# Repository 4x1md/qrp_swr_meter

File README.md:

# QRP SWR Meter for Yaesu FT-817ND

## Overview

This QRP SWR meter was designed for using with my Yaesu FT-817ND transceiver. Actually, it is antenna impedance meter based on Wheatstone bridge where antenna represents the unknown resistance. The bridge is built with six 2W resistors thus it can handle up to 16W of transmitting power.

This SWR-meter design has one big disadvantage: each time when SWR measurement is required, the device has to be switched from bypass to measurement mode. After antenna tuner alignment it has to be switched to bypass mode again. Real-time SWR monitoring is impossible with this type of SWR-meters. However, the Wheatstone bridge uses widely available resistors and does not require winding any coils. It makes such devices easy to build and can be considered an advantage.

## Schematic

## Reference Circuits

This project is not the first of this kind. My main source of inspiration was [Wideband SWR meter by Manfred Mornhinweg XQ6FOD](http://ludens.cl/Electron/swr/swr.html).

Other similar circuits can be found in [links section](#links) of this document and on the internet.

## Parts

In general, this circuit requires widely available easy to get parts.

The microampermeter I used for SWR indication is actually a tuning indicator from an old radio receiver. Its full deflection current is 250uA and internal resistance is about 1.2K. These values are not critical and almost any microampermeter.

Circuit alignment showed that more critical parts are diodes. The first diodes I used were BAT49 Schottky diodes. Later, due to their high capacity I had to replace them with germanium 1N60P.

## PCB Design

The PCB was designed using KiCAD software.

## Photo Gallery & Development History

### First Prototype

The first prototype was build on a random size PCB designed in KiCad Eschema. It used through hole mounted SMA female connectors.

At first, its performance was constantly starting to deteriorate at frequencies of 12-13MHz and higher. The investigation showed two main reasons:

1. I didn't clean well the PCB after soldering and the remaining flux caused current leakage at higher frequencies.
2. I used diodes with high capacity (more than 100pF).

The PCB was made at home using [toner transfer method](http://www.instructables.com/id/Cheap-and-Easy-Toner-Transfer-for-PCB-Making/).

### Second Prototype

After getting the previous prototype to work well, I decided to put the device in an enclosure box. For that matter I chose a 83x58x35mm plastic box with transparent cover which is sold cheap on AliExpress.

I had to redesign the PCB to match the inner dimensions of the box. I also decided to use right angle SMA connectors in this design. As a result I got the following prototype.

### Factory Produced PCB

Later I decided to try to order a factory produced PCB. I ordered a small quantity from ITEAD Studio. As to my taste, they did a great job.

The board fits the box perfectly.

:warning: **Important Note!**
Minimum order at the factory was 10 boards from which I need only two. As of December 1, 2016, I have 8 boards, which I can give away. If you'd like to build this SWR-meter for yourself, I can send you a board. Feel free to contact me. 

### Assembled Device

### PCB Prototypes History

All my home-made PCB prototypes in two photos.

## Links

1. [Wideband SWR meter by Manfred Mornhinweg XQ6FOD](http://ludens.cl/Electron/swr/swr.html) ([circuit 1](http://users.belgacom.net/hamradio/schemas/swrmeter.GIF))
2. [Circuit 2](https://yd1chs.files.wordpress.com/2008/12/qrp-vswr-meter-schematic.jpg)
3. [Circuit 3](http://www.radars.me.uk/Pictures/linear/Powermeter.jpg)
4. [Circuit 4](http://www.circuitdiagramworld.com/uploads/allimg/201411/135-8956_471946937.png)
5. [Measurements on Balanced Lines Using the Noise Bridge & SWR Meter by Lloyd Butler VK5BR. Amateur Radio, July 1992](http://users.tpg.com.au/users/ldbutler/MeasBalLine.htm)
6. [Low-power antenna tuner and SWR meter](http://www.tradeofic.com/Circuit/8224-LOW_POWER_ANTENNA_TUNER_AND_SWR_METER.html)
7. [Simple LED SWR bridge by John Young G0WGR](http://www.qsl.net/om3cug/swr_led/swr_meter_led_g0wqr.jpg)
8. [Измеритель КСВ by LY3BG](http://www.cqham.ru/ksw.html)
9. [КСВ-метры: теория и практика. Как сделать достоверный КСВ-метр by UT1MA](http://www.cqham.ru/ma1.phtml)
10. [Cheap and Easy Toner Transfer for PCB Making](http://www.instructables.com/id/Cheap-and-Easy-Toner-Transfer-for-PCB-Making/)
11. [Easy, Consistent & Cheap Toner Transfer Method for Single & Double Sided PCBs](http://www.instructables.com/id/Easy-Consistent-Cheap-Toner-Transfer-Method-for-Si/)

## Questions? Suggestions?
You are more than welcome to contact me with any questions, suggestions or propositions regarding this project. You can:

1. Visit [my QRZ.COM page](https://www.qrz.com/db/4X5DM)
2. Visit [my Facebook profile](https://www.facebook.com/Dima.Meln)
3. Write me an email to iosaaris =at= gmail dot com

## How to Support or Say Thanks

If you like this project, or found here some useful information and want to say thanks, or encourage me to do more, you can buy me a coffee!

You can aslo make a donation with PayPal:

---

**73 de 4X1MD ex 4X5DM**

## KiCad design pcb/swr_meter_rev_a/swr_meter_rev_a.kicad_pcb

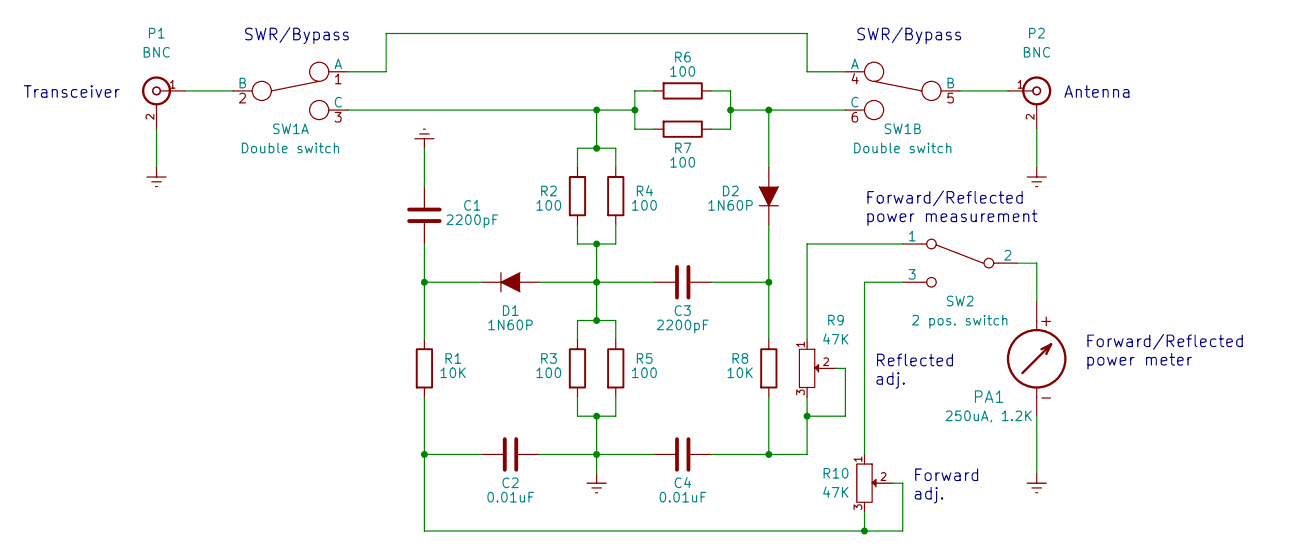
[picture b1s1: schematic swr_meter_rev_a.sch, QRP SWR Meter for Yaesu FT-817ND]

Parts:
C1: 2200pF; Capacitor_Disc_D6_P5
C2, C4: 0.01uF; Capacitor_Disc_D6_P5
C3: 2200pF; Capacitor_Disc_D6_P7.5
D1, D2: 1N60P; Diode_DO-35_SOD27_Horizontal_RM10
P1, P2: BNC; SMB_Straight
PA1: 250uA, 1.2K; Microampermeter
R1, R8: 10K; Resistor_Horizontal_RM10mm
R2, R3, R4, R5, R6, R7: 100; Resistor_Horizontal_2W
R9, R10: 47K; Potentiometer_Triwood_RM-065
SW1: Double switch; Tumbler_SW_x2
SW2: 2 pos. switch; Tumbler_SW

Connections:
GNDREF: C1.1, C2.1, C4.1, P1.2 (Ext), P2.2 (Ext), PA1.2 (-), R3.2, R5.2
unnamed: C1.2, D1.1 (K), R1.1
unnamed: C2.2, R1.2, R10.2, R10.3
unnamed: C3.1, D1.2 (A), R2.2, R3.1, R4.2, R5.1
unnamed: C3.2, D2.1 (K), R8.1
unnamed: C4.2, R8.2, R9.2, R9.3
unnamed: D2.2 (A), R6.1, R7.1, SW1.6 (C)
unnamed: P1.1 (In), SW1.2 (B)
unnamed: P2.1 (In), SW1.5 (B)
unnamed: PA1.1 (+), SW2.2
unnamed: R2.1, R4.1, R6.2, R7.2, SW1.3 (C)
unnamed: R9.1, SW2.1
unnamed: R10.1, SW2.3
unnamed: SW1.1 (A), SW1.4 (A)

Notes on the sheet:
Forward/Reflected power meter
Antenna
Transceiver
Forward/Reflected power measurement
SWR/Bypass
Forward adj.
Reflected adj.

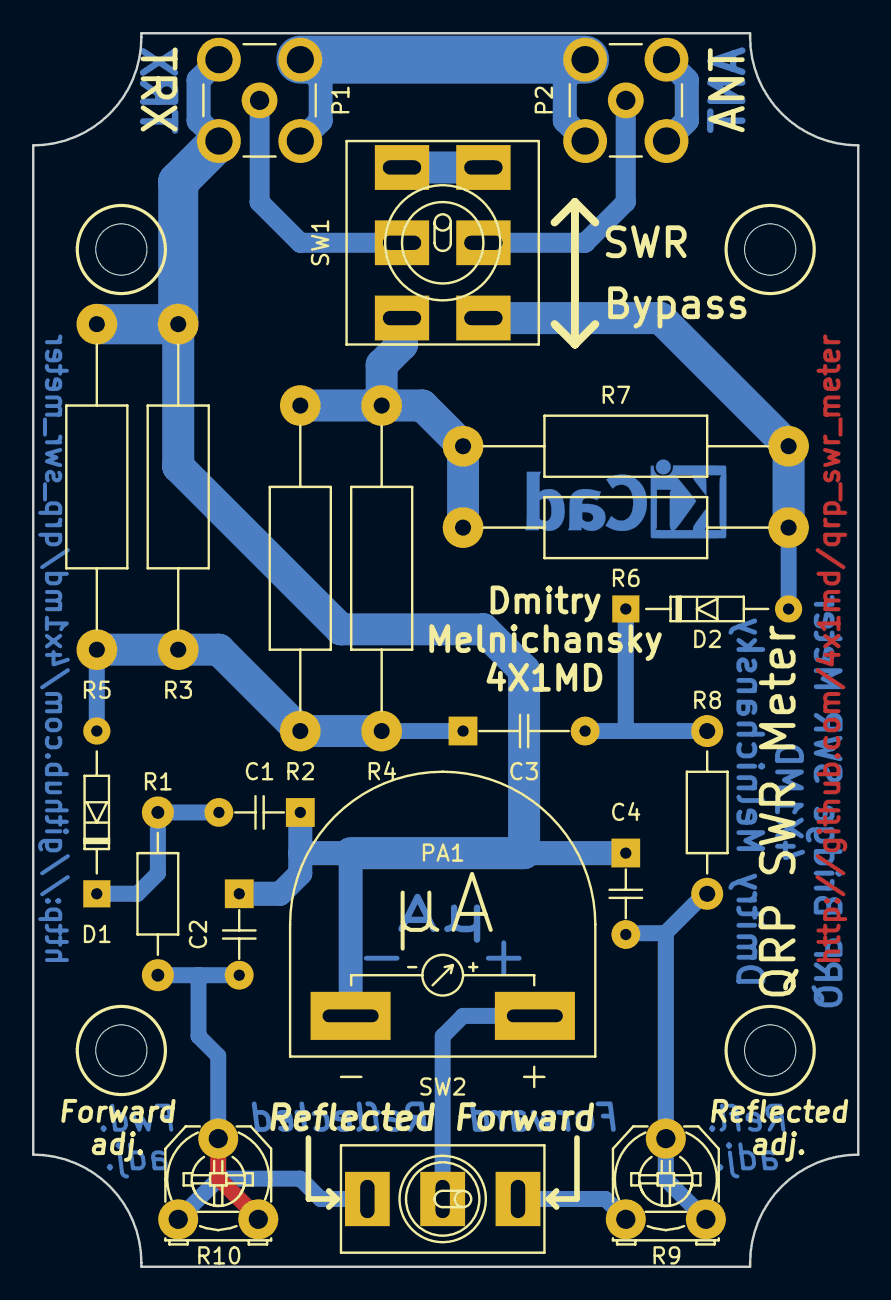
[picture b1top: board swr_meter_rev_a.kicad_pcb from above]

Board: 2 copper layers, 51.5 x 77.0 mm, 25 parts (0 on the bottom side), 14 nets.

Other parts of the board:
MH1, MH2, MH3, MH4: MH_3.2mm_M3; MountingHole_3.2mm_M3

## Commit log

2016-09-24 Shematics, PCB and gerbers.
2016-09-24 README.md
2016-11-30 README.md and images.
2016-11-30 PCB photo.
2017-12-02 KiCAD files moved to pcb directory.
2017-12-02 README.md and deleting not required files.
2017-12-07 Corrected URLs on the PCB.
2017-12-12 Silkprint corrections and new gerbers.
2021-01-23 3D model images from KiCAD 5.
